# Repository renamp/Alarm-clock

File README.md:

# Alarm-clock
Alarm clock with microcontroller atmega8, RTC module and DFplayer module.

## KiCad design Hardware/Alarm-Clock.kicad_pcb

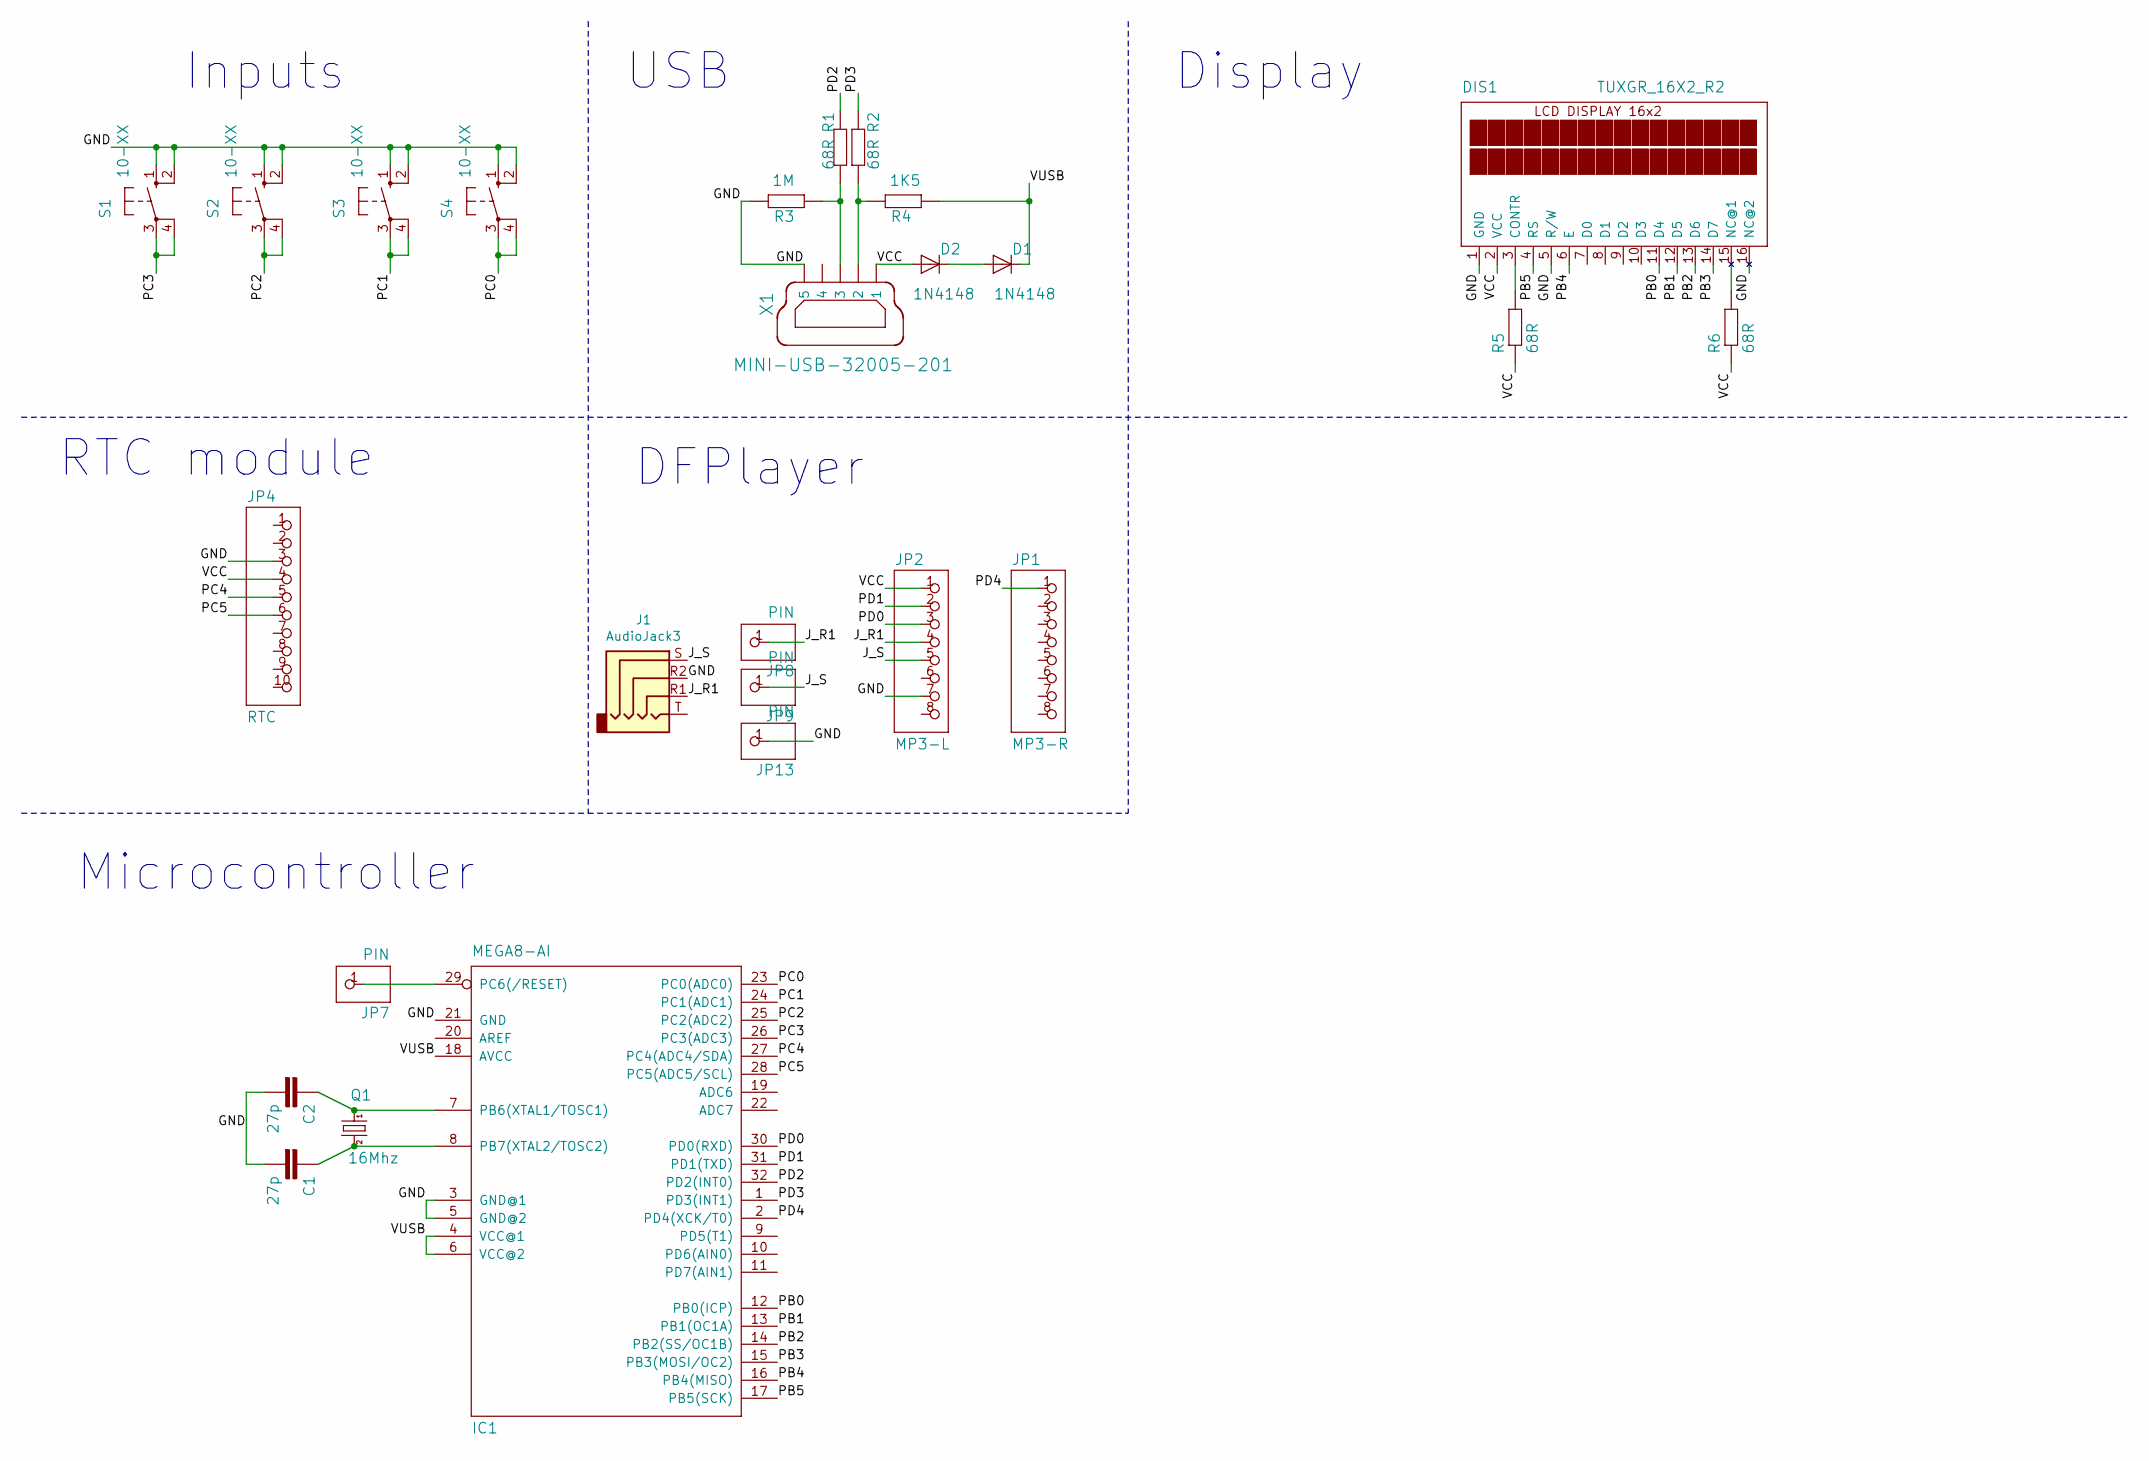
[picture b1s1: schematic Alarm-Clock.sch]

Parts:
C1, C2: 27p; C025-024X044
D1, D2: 1N4148; DO35-7
DIS1: TUXGR_16X2_R2
IC1: MEGA8-AI; TQFP-32_7x7mm_P0.8mm
J1: AudioJack3; Jack_3.5mm_PJ320D_Horizontal
JP1: MP3-R; 1X08
JP2: MP3-L; 1X08
JP4: RTC; 1X10
JP7, JP8, JP9, JP13: PIN; 1X01
Q1: 16Mhz; HC49_S
R1, R2, R6: 68R; 0204_7
R3: 1M; 0204_5
R4: 1K5; 0204_7
R5: 68R; 0204_5
S1, S2, S3, S4: 10-XX; B3F-10XX
X1: MINI-USB-32005-201; 32005-201

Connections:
/GND: C1.2, C2.2, DIS1.1 (GND), DIS1.5 (R/W), DIS1.16 (NC@2), IC1.3 (GND@1), IC1.5 (GND@2), IC1.21 (GND), J1.R2, JP2.7, JP4.3, JP13.1, R3.2, S1.1 (S), S1.2 (S1), S2.1 (S), S2.2 (S1), S3.1 (S), S3.2 (S1), S4.1 (S), S4.2 (S1), X1.5
/J_R1: J1.R1, JP2.4, JP8.1
/J_S: J1.S, JP2.5, JP9.1
/PB0: DIS1.11 (D4), IC1.12 (PB0(ICP))
/PB1: DIS1.12 (D5), IC1.13 (PB1(OC1A))
/PB2: DIS1.13 (D6), IC1.14 (PB2(SS/OC1B))
/PB3: DIS1.14 (D7), IC1.15 (PB3(MOSI/OC2))
/PB4: DIS1.6 (E), IC1.16 (PB4(MISO))
/PB5: DIS1.4 (RS), IC1.17 (PB5(SCK))
/PC0: IC1.23 (PC0(ADC0)), S4.3, S4.4 (P1)
/PC1: IC1.24 (PC1(ADC1)), S3.3, S3.4 (P1)
/PC2: IC1.25 (PC2(ADC2)), S2.3, S2.4 (P1)
/PC3: IC1.26 (PC3(ADC3)), S1.3, S1.4 (P1)
/PC4: IC1.27 (PC4(ADC4/SDA)), JP4.5
/PC5: IC1.28 (PC5(ADC5/SCL)), JP4.6
/PD0: IC1.30 (PD0(RXD)), JP2.3
/PD1: IC1.31 (PD1(TXD)), JP2.2
/PD2: IC1.32 (PD2(INT0)), R1.1
/PD3: IC1.1 (PD3(INT1)), R2.1
/PD4: IC1.2 (PD4(XCK/T0)), JP1.1
/VCC: D2.A, DIS1.2 (VCC), JP2.1, JP4.4, R5.1, R6.1, X1.1
/VUSB: D1.C, IC1.4 (VCC@1), IC1.6 (VCC@2), IC1.18 (AVCC), R4.1
unnamed: C1.1, IC1.8 (PB7(XTAL2/TOSC2)), Q1.2
unnamed: C2.1, IC1.7 (PB6(XTAL1/TOSC1)), Q1.1
unnamed: D1.A, D2.C
unnamed: DIS1.3 (CONTR), R5.2
unnamed: DIS1.15 (NC@1), R6.2
unnamed: IC1.29 (PC6(/RESET)), JP7.1
unnamed: R1.2, R3.1, X1.3
unnamed: R2.2, R4.2, X1.2

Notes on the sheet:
Inputs
USB
Display
RTC module
DFPlayer
Microcontroller

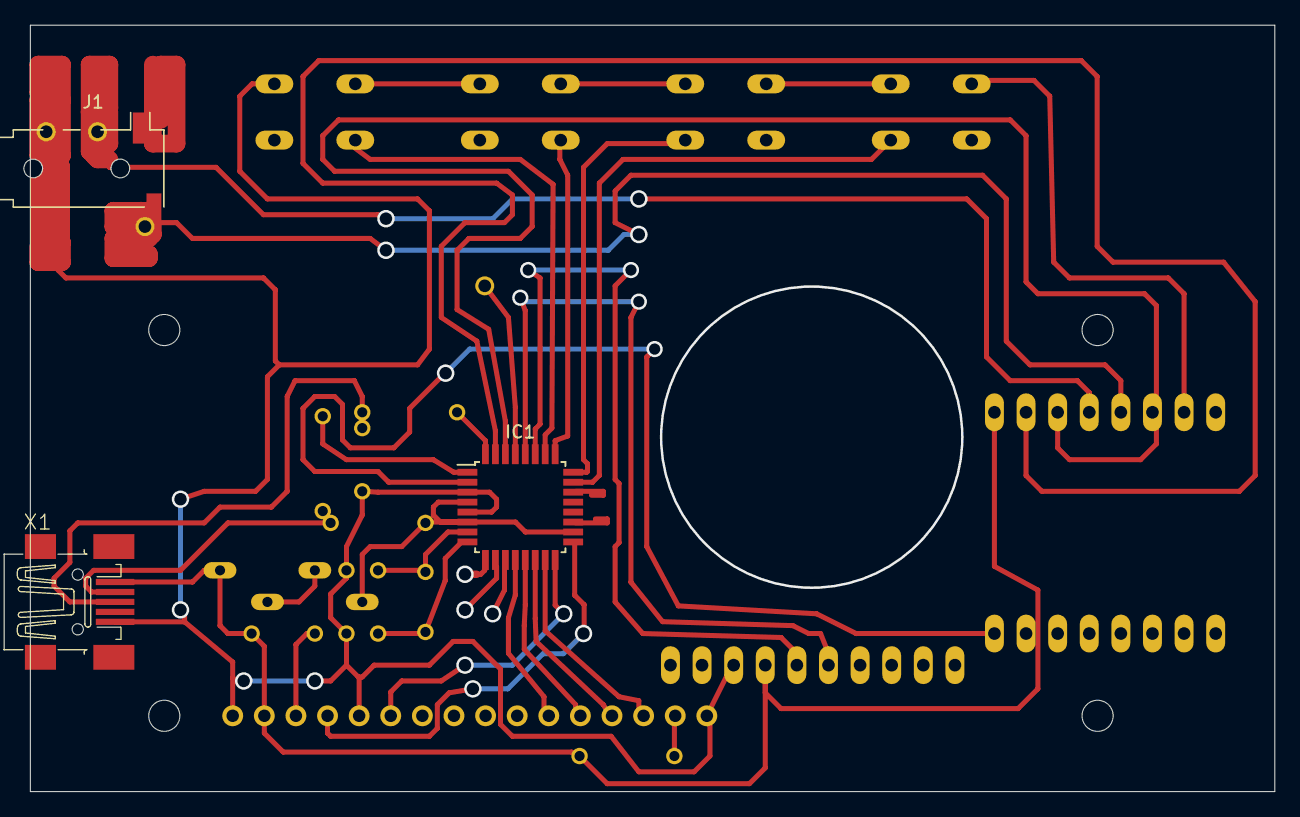
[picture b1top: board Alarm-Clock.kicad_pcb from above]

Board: 2 copper layers, 100.0 x 61.6 mm, 26 parts (0 on the bottom side), 30 nets.

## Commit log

2021-12-01 add gitignore
2021-12-02 update schematic and board
2021-12-05 Added 3d models to board
2021-12-05 edit gitignore
2021-12-09 Created Case
